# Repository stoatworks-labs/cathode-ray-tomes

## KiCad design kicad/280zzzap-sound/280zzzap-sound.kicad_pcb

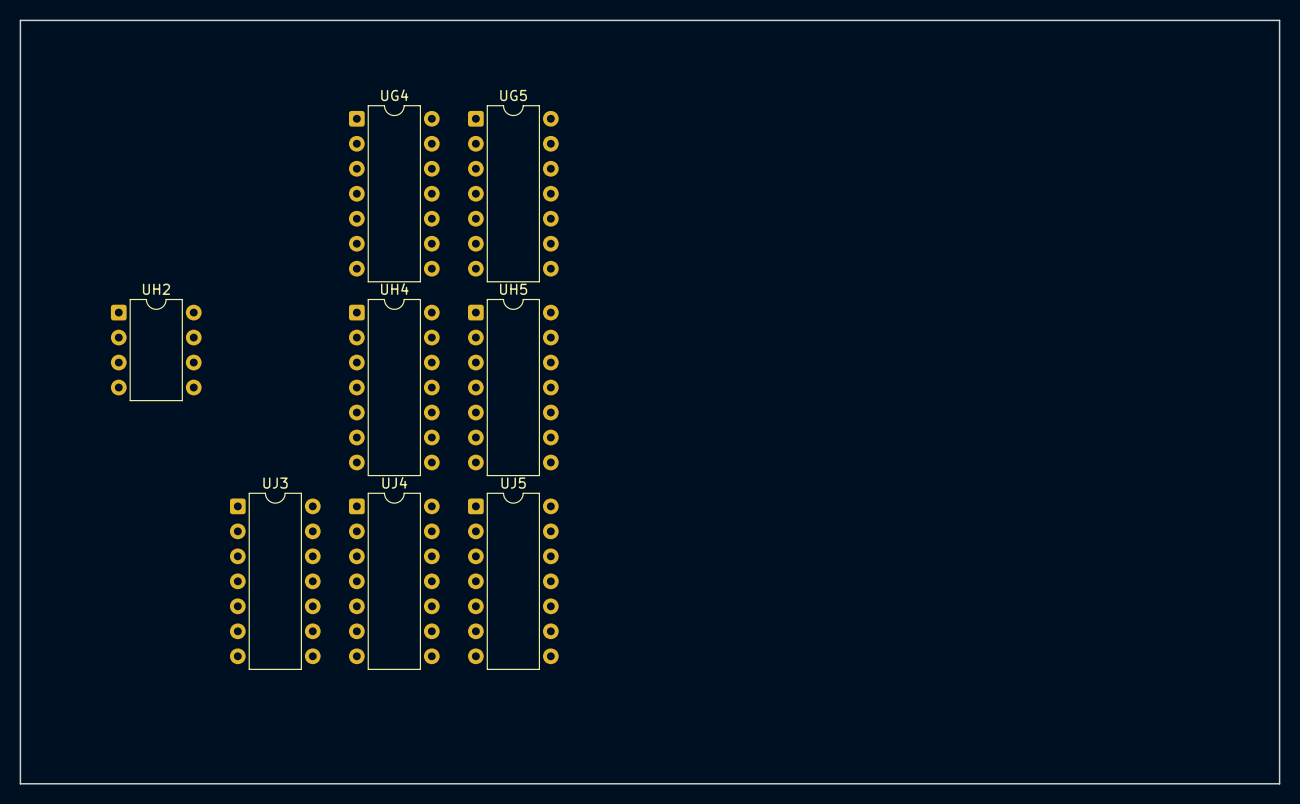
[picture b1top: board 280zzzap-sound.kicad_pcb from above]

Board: 2 copper layers, 128.0 x 77.6 mm, 8 parts (0 on the bottom side), 12 nets, no tracks yet.

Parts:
UG4, UG5: CD4016; DIP-14_W7.62mm
UH2: MC3340; DIP-8_W7.62mm
UH4, UH5: LM3900; DIP-14_W7.62mm
UJ3, UJ5: LM3900; DIP-14_W7.62mm
UJ4: CD4016; DIP-14_W7.62mm

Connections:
+5V: UG4.14, UG5.14, UH4.14, UH5.14, UJ3.14, UJ4.14, UJ5.14
GND: UG4.7, UG5.1, UG5.7, UH2.3, UH4.7, UH5.7, UJ3.7, UJ4.7, UJ5.7
unnamed: UG4.8, UH5.4
unnamed: UG5.3, UG5.8
unnamed: UG4.4, UH4.10
unnamed: UJ3.5, UJ4.13
unnamed: UJ3.10, UJ4.5
unnamed: UJ4.12, UJ5.5
unnamed: UG5.4, UH5.11
unnamed: UJ3.2, UJ4.2
unnamed: UJ3.13, UJ4.3
unnamed: UJ4.11, UJ5.2

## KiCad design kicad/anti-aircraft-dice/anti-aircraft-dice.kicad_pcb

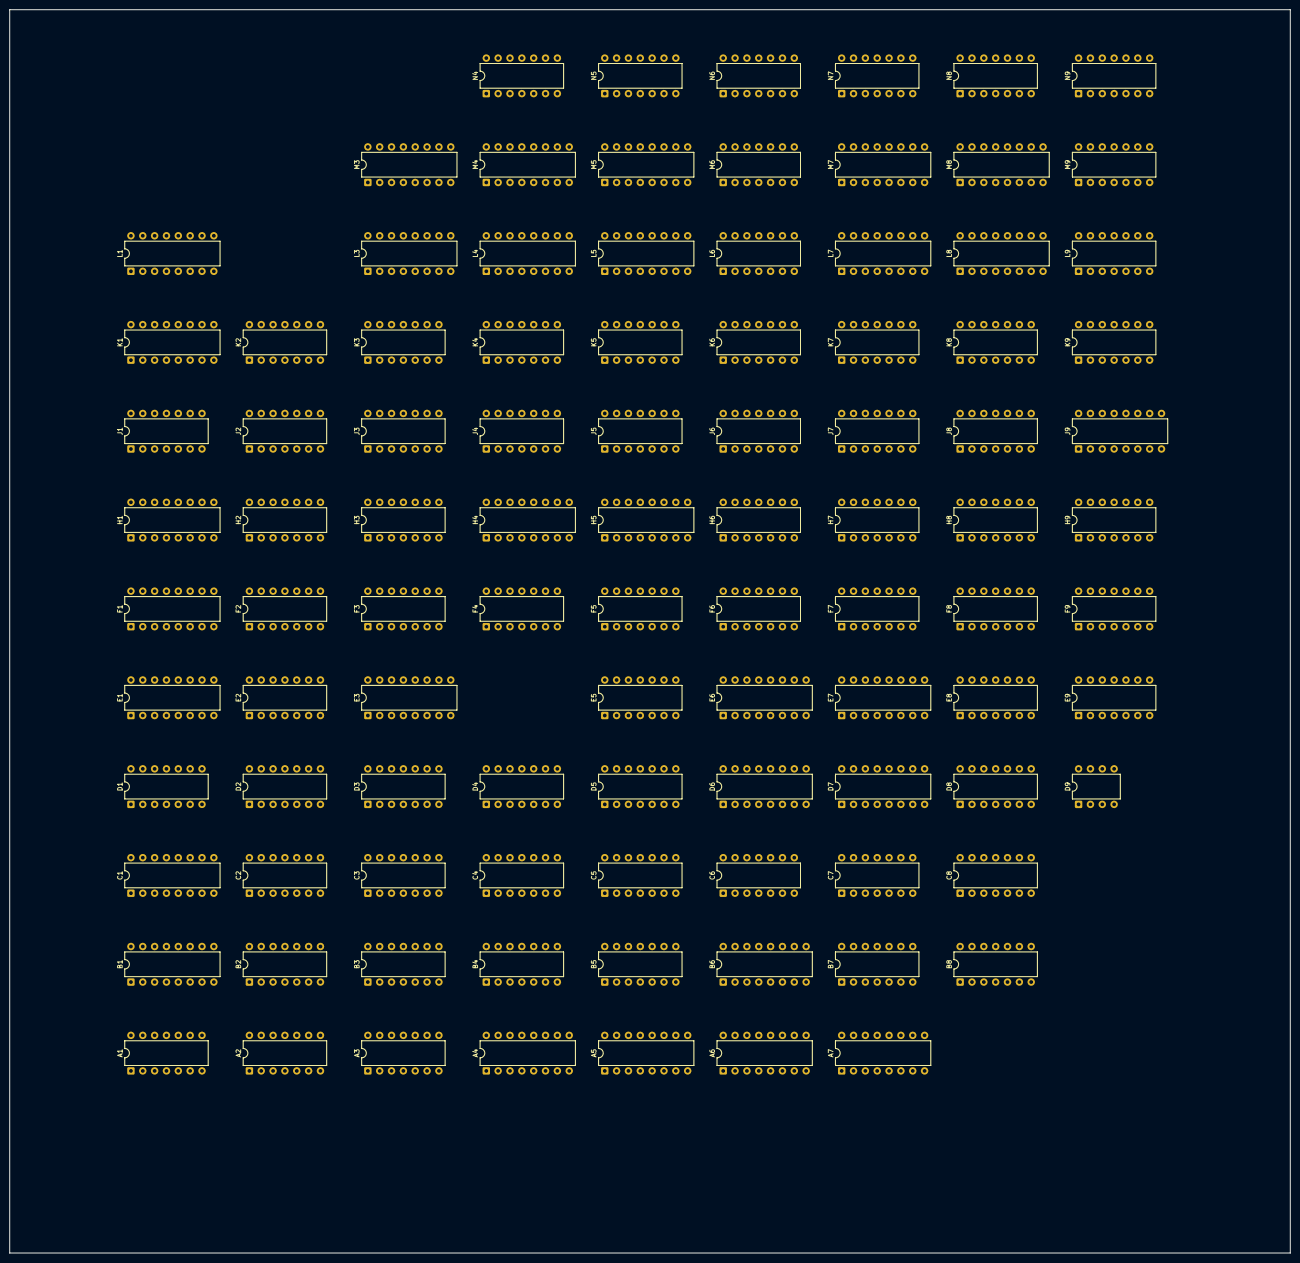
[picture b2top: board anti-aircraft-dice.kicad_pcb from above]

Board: 2 copper layers, 274.6 x 266.6 mm, 97 parts (0 on the bottom side), 319 nets, no tracks yet.

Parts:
A1: 7402; DIP-14_W7.62mm
A2: 7408; DIP-14_W7.62mm
A3: 7493; DIP-14_W7.62mm
A4, A5: 74153; DIP-16_W7.62mm
A6: 7448; DIP-16_W7.62mm
A7: 9312; DIP-16_W7.62mm
B1: 9602; DIP-16_W7.62mm
B2, B8: 7400; DIP-14_W7.62mm
B3: 7474; DIP-14_W7.62mm
B4, B5: 7490; DIP-14_W7.62mm
B6: 9312; DIP-16_W7.62mm
B7: 7402; DIP-14_W7.62mm
C1: 9602; DIP-16_W7.62mm
C2: 7400; DIP-14_W7.62mm
C3: 7402; DIP-14_W7.62mm
C4, C5: 7490; DIP-14_W7.62mm
C6: 7486; DIP-14_W7.62mm
C7: 7410; DIP-14_W7.62mm
C8: 7404; DIP-14_W7.62mm
D1, D8: 7474; DIP-14_W7.62mm
D2: 7427; DIP-14_W7.62mm
D3, D4: 7420; DIP-14_W7.62mm
D5: 7402; DIP-14_W7.62mm
D6, D7: 9316; DIP-16_W7.62mm
D9: 555; DIP-8_W7.62mm
E1: 9602; DIP-16_W7.62mm
E2: 7404; DIP-14_W7.62mm
E3, E6, E7: 9316; DIP-16_W7.62mm
E5: 7486; DIP-14_W7.62mm
E8: 7408; DIP-14_W7.62mm
E9: 7474; DIP-14_W7.62mm
F1: 9316; DIP-16_W7.62mm
F2, F7: 74107; DIP-14_W7.62mm
F3: 7402; DIP-14_W7.62mm
F4: 7408; DIP-14_W7.62mm
F5, F8: 7474; DIP-14_W7.62mm
F6: 7400; DIP-14_W7.62mm
F9: 7404; DIP-14_W7.62mm
H1, H4, H5: 9316; DIP-16_W7.62mm
H2: 7408; DIP-14_W7.62mm
H3, H9: 7400; DIP-14_W7.62mm
H6: 7420; DIP-14_W7.62mm
H7: 7402; DIP-14_W7.62mm
H8: 7432; DIP-14_W7.62mm
J1, J2: 7486; DIP-14_W7.62mm
J3: 7402; DIP-14_W7.62mm
J4, J5, J8: 7474; DIP-14_W7.62mm
J6: 74107; DIP-14_W7.62mm
J7: 7400; DIP-14_W7.62mm
J9: 74153; DIP-16_W7.62mm
K1: 82S123; DIP-16_W7.62mm
K2, K8, K9: 7474; DIP-14_W7.62mm
K3: 7404; DIP-14_W7.62mm
K4, K5: 7493; DIP-14_W7.62mm
K6: 7410; DIP-14_W7.62mm
K7: 7486; DIP-14_W7.62mm
L1: 9312; DIP-16_W7.62mm
L3, L4, L5: 74153; DIP-16_W7.62mm
L6: 7402; DIP-14_W7.62mm
L7, L8: 9316; DIP-16_W7.62mm
L9: 7400; DIP-14_W7.62mm
M3, M4: 7485; DIP-16_W7.62mm
M5: 74153; DIP-16_W7.62mm
M6: 7400; DIP-14_W7.62mm
M7, M8: 9316; DIP-16_W7.62mm
M9: 7408; DIP-14_W7.62mm
N4: 7404; DIP-14_W7.62mm
N5: 7450; DIP-14_W7.62mm
N6, N9: 7402; DIP-14_W7.62mm
N7: 7408; DIP-14_W7.62mm
N8: 7400; DIP-14_W7.62mm

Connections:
+5V: A1.14, A2.14, A3.5, A4.16, A5.16, A6.16, A7.16, B2.14, B3.14, B4.5, B5.5, B6.16, B7.14, B8.14, C2.14, C3.14, C4.5, C5.5, C6.14, C7.14, C8.14, D1.14, D2.14, D3.14, D4.14, D5.14, D6.16, D7.16, D8.14, D9.8, E2.14, E3.16, E5.14, E6.16, E7.16, E8.14, E9.14, F1.16, F2.14, F3.14, F4.14, F5.14, F6.14, F7.14, F8.14, F9.14, H1.16, H2.14, H3.14, H4.16, H5.16, H6.14, H7.14, H8.14, H9.14, J1.14, J2.14, J3.14, J4.14, J5.14, J6.14, J7.14, J8.14, J9.16, K1.16, K2.14, K3.14, K4.5, K5.5, K6.14, K7.14, K8.14, K9.14, L1.16, L3.16, L4.16, L5.16, L6.14, L7.16, L8.16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
A1-1: A1.1, C8.1
A1-3: A1.3, A1.4, A3.2, A3.3
A1-9: A1.9, A1.13, A2.10, A2.12
A1-10: A1.10, A1.11
A2-2: A2.2, A2.8
A2-3: A2.3, B1.4
A2-4: A2.4, A2.11
A2-6: A2.6, B1.12
A3-1: A3.1, A3.12
A4-3: A4.3, B4.1, B4.12
A4-4: A4.4, B5.1, B5.12
A4-5: A4.5, C4.1, C4.12
A4-6: A4.6, C5.1, C5.12
A4-7: A4.7, A6.7
A4-9: A4.9, A6.1
A4-10: A4.10, C5.9
A4-11: A4.11, C4.9
A4-12: A4.12, B5.9
A4-13: A4.13, B4.9
A5-3: A5.3, B4.8
A5-4: A5.4, B5.8
A5-5: A5.5, C4.8
A5-6: A5.6, C5.8
A5-7: A5.7, A6.2
A5-9: A5.9, A6.6
A5-10: A5.10, C5.11
A5-11: A5.11, C4.11, C5.14
A5-12: A5.12, B5.11
A5-13: A5.13, B4.11, B5.14
A6-4: A6.4, B7.4
A6-9: A6.9, B6.5
A6-10: A6.10, A7.9
A6-11: A6.11, B6.9
A6-12: A6.12, B6.4
A6-13: A6.13, A7.1
A6-14: A6.14, A7.4
A6-15: A6.15, B6.1
A7-15: A7.15, B7.9
ATTRACT: A1.2, C3.9, C3.12, D8.9, E8.2, E9.3, E9.11, H7.2
ATTRACT_n: B3.12, D8.8, H9.2, H9.12, K8.4, K8.13, K9.4, K9.13
B1-3: B1.3, C1.7
B1-5: B1.5, B2.4, B2.11, C3.11
B1-11: B1.11, B2.5, B2.8, C3.8
B1-13: B1.13, C1.9
B2-3: B2.3, B3.11
B3-2: B3.2, B8.11
B3-3: B3.3, C8.10
B4-14: B4.14, C3.13
B6-15: B6.15, B7.8
B7-1: B7.1, B8.2
B7-3: B7.3, C7.12
B7-6: B7.6, C7.8
B7-10: B7.10, B8.12
B7-13: B7.13, D6.3
B8-3: B8.3, B8.13
B8-4: B8.4, D7.15, J7.9, K6.3
B8-5: B8.5, D6.15, D7.7
B8-6: B8.6, C3.2, D6.9, D7.9
C2-2: C2.2, E2.9, F4.6, H3.12
C2-3: C2.3, E6.4
C2-4: C2.4, D1.2, D1.6, D2.5
C2-5: C2.5, D1.8, D2.9
C2-8: C2.8, D1.1
C2-10: C2.10, D2.10, E2.12
C2-11: C2.11, D1.13
C2-13: C2.13, D2.4, E2.13, E3.14
C3-1: C3.1, F6.5
C3-3: C3.3, C3.5, E6.9, E7.9, F6.3
C3-6: C3.6, K6.6
C3-10: C3.10, C4.14
C6-6: C6.6, D5.12
C6-11: C6.11, C7.9
C7-2: C7.2, C7.4, E8.8
C7-3: C7.3, C8.6
C7-11: C7.11, C8.8
C8-4: C8.4, N5.9
CLOCK: E6.2, E7.2, H4.2, H5.2, J4.9, M7.2, M8.2
CLOCK_n: F1.2, H1.2, J4.3, J4.8, J4.12, N7.10, N7.12
COMP_HIT_n: C2.6, E1.5
COMP_SYNC: B3.1, E1.13, J2.3
D2-3: D2.3, D2.11, D3.6
D2-6: D2.6, F3.8
D2-8: D2.8, F3.9
D3-1: D3.1, H2.11
D3-2: D3.2, E3.13
D3-4: D3.4, E3.12
D3-5: D3.5, E3.11
D3-10: D3.10, D3.12, D3.13
D4-1: D4.1, D5.13
D4-2: D4.2, E5.6
D4-6: D4.6, F4.9
D5-1: D5.1, D6.5
D5-3: D5.3, D5.4, D6.4
D5-8: D5.8, E5.3, E5.9
D5-9: D5.9, E5.10, E5.11
D5-10: D5.10, D5.11
D6-1: D6.1, D7.1, F6.11
D8-2: D8.2, E8.3
D8-10: D8.10, D9.4, E8.11
D8-11: D8.11, F9.12
D9-3: D9.3, F9.13
DELAY_L: C1.10, H8.12
DELAY_R: C1.6, H8.2
DIR_SELECT_n: F2.3, H3.2, J1.2, J1.4, J1.10, J1.12
E1-7: E1.7, K2.13
E1-11: E1.11, N9.4
E2-2: E2.2, E3.3
E2-3: E2.3, F3.10
E2-8: E2.8, E6.5
E2-10: E2.10, E3.9
E2-11: E2.11, E3.15
E3-10: E3.10, H2.13, J2.11
E5-5: E5.5, E5.8
E6-1: E6.1, E7.1, F5.5, F7.13
E6-3: E6.3, H3.11
E6-15: E6.15, E7.7, F6.2
E7-15: E7.15, F7.12, M9.1
E8-12: E8.12, F8.2, F9.4
E9-1: E9.1, E9.13, F8.9
E9-5: E9.5, E9.12
F1-7: F1.7, H1.15, H3.4
F1-9: F1.9, H1.9, H3.6
F1-15: F1.15, F2.9, H2.2
F2-2: F2.2, F3.3
F2-5: F2.5, H2.1
F3-1: F3.1, H1.6
F3-11: F3.11, J7.8
F3-12: F3.12, F6.8
F4-3: F4.3, F5.3
F4-10: F4.10, F6.6
F6-1: F6.1, F6.10, M9.3
F7-3: F7.3, M9.2
F7-5: F7.5, M9.10
F7-9: F7.9, M7.15, M9.9
F7-10: F7.10, M7.1, M8.1, N8.3
F8-4: F8.4, F9.3
F8-5: F8.5, F8.12
F9-1: F9.1, N5.4, N5.10, N6.13
F9-2: F9.2, N6.5
FIRE_LEFT: F5.1, H7.5, J8.8, J9.15
FIRE_LEFT_n: F6.13, J8.9
FIRE_RIGHT: H7.6, J8.6, J9.1
FIRE_RIGHT_n: J8.5, M6.4, N8.1
FLASH: A3.8, E5.4, K7.9
GND: A1.7, A2.7, A3.10, A4.1, A4.8, A4.15, A5.1, A5.8, A5.15, A6.8, A7.2, A7.3, A7.5, A7.6, A7.7, A7.8, B2.7, B3.7, B4.6, B4.7, B4.10, B5.6, B5.7, B5.10, B6.2, B6.3, B6.6, B6.7, B6.8, B7.7, B8.7, C1.4, C1.12, C2.7, C3.7, C4.6, C4.7, C4.10, C5.6, C5.7, C5.10, C6.7, C7.7, C8.7, D1.7, D2.7, D3.7, D4.7, D5.7, D6.8, D7.3, D7.4, D7.5, D7.6, D7.8, D8.7, D9.1, E1.12, E2.7, E3.4, E3.5, E3.8, E5.7, E6.6, E6.8, E7.5, E7.6, E7.8, E8.7, E9.7, F1.5, F1.6, F1.8, F2.7, F3.7, F4.7, F5.7, F6.7, F7.7, F8.7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
H1: C8.11, H4.14, J9.14, K8.2, K9.2, L5.6, M5.6
H1-5: H1.5, H3.3
H2: B6.11, H4.13, J9.2, K8.12, K9.12, L5.5, L5.10, M5.5, M5.10
H2-3: H2.3, H2.10, H3.5
H3-8: H3.8, L1.10
H4: B6.12, H4.12, J5.11, L3.6, L4.6, L5.4, L5.11, M5.4, M5.11
H4-15: H4.15, H5.7
H5-15: H5.15, J6.12
H6-1: H6.1, H7.13
H6-2: H6.2, K7.8
H6-6: H6.6, M9.13
H6-8: H6.8, J4.2
H7-3: H7.3, H7.4
H7-8: H7.8, K7.6, K7.12
H7-9: H7.9, K7.3, K7.13
H7-10: H7.10, H7.11
H7-12: H7.12, J2.6
H8: A7.10, B6.10, F4.2, H4.11, H6.9, L3.5, L3.10, L4.5, L4.10, L5.12, M5.12
H8-1: H8.1, H9.6
H8-3: H8.3, J8.1
H8-11: H8.11, J8.13
H8-13: H8.13, H9.8
H9-1: H9.1, L9.11
H9-3: H9.3, J9.5
H9-4: H9.4, J9.7, K9.3, K9.11
H9-9: H9.9, J9.9, K8.3, K8.11
H9-11: H9.11, J9.11
H9-13: H9.13, N9.1
H16: A4.14, A5.14, A6.5, F4.1, H5.14, J2.10, K3.5
H16_n: K3.6, L3.4, L3.11, L4.4, L4.11
H32: A4.2, A5.2, C6.1, H5.13, J2.9
H64: C6.13, H5.12, H6.10, J3.6, K3.3
H64_n: K3.4, L3.12, L4.12
H128: C6.9, H5.11, H6.12, J5.12
H128_xor_H256: C6.8, C7.10, C8.13
H128_xor_H256_n: B8.1, C8.12, M6.1
H256: C6.2, C6.10, C6.12, H6.13, J5.10, J6.3, N7.9
H256_n: J6.2, N7.13
H256_xor_H32: B7.2, C6.3, C8.9, N6.6
HIT_DETECT: B2.1, B2.2, B2.6, C2.9, C2.12
HRESET: J3.2, J4.6, J5.3, K4.14
HRESET_n: H4.1, H5.1, J4.5, J6.13
HSYNC: D6.2, D7.2, J2.1, J3.3, J3.4, K2.11, L7.2, L8.2
HSYNC_n: J3.1, J3.5, J7.5
J1-3: J1.3, K1.12
J1-6: J1.6, K1.11
J1-8: J1.8, K1.13
J1-11: J1.11, K1.10
J2-8: J2.8, M6.2
J4-11: J4.11, N4.4
J5-2: J5.2, K6.8
J5-8: J5.8, N8.2
J7-2: J7.2, J7.6, J7.12
J7-3: J7.3, J8.4
J7-11: J7.11, J8.10
K1-1: K1.1, L1.1
K1-2: K1.2, L1.2
K1-3: K1.3, L1.3
K1-4: K1.4, L1.4
K1-5: K1.5, L1.5
K1-6: K1.6, L1.6
K1-7: K1.7, L1.7
K1-9: K1.9, L1.9
K6-12: K6.12, N9.8
K6-13: K6.13, L8.15, L9.9, M6.12
K7-10: K7.10, K7.11
L3-7: L3.7, M3.13
L3-9: L3.9, M3.15
L4-7: L4.7, M4.13
L4-9: L4.9, M4.15
L5-7: L5.7, M3.10
L5-9: L5.9, M3.12
L6-1: L6.1, L7.5
L6-2: L6.2, L6.13, L7.4
L6-5: L6.5, M6.11
L6-6: L6.6, M6.8
L6-10: L6.10, L7.3
L7-1: L7.1, L8.1, M6.6
L7-9: L7.9, L8.9, L9.8, N9.12
L7-15: L7.15, L8.7, L9.10
L9-2: L9.2, N9.13
L9-3: L9.3, M9.12
L9-4: L9.4, M7.7, M8.15
L9-5: L9.5, M6.9, M9.8
L9-6: L9.6, M7.9, M8.9, N9.9, N9.11
L9-12: L9.12, L9.13
LA: H3.13, K8.5, L3.14, L5.14, N6.2
LARGE_LEFT_MISSILE: B2.10, C3.4, J7.13
LARGE_RIGHT_MISSILE: B2.13, J7.1, N9.10
LA_or_LB: B7.12, C2.1, N4.10, N5.5
LB: K8.9, L3.2, L5.2, N6.3
LB_n: D5.6, K8.8
LEFT_MISSILE_WIN: A2.5, D4.5, F3.13
LEFT_MISSILE_n: B8.9, F4.8
LMH1: C6.5, E6.14
LMH2: E5.12, E6.13
LMH3: E5.13, E6.12
LMH4: E6.11, F6.9
LMV1: C6.4, D6.14
LMV2: D6.13, E5.1
LMV3: D6.12, E5.2, K6.5
LMV4: D6.11, J7.10, K6.4
LT_HIT: A1.5, B1.10, B7.11, C1.11, D4.4, D5.2, D5.5
LT_HIT_n: A2.13, B1.9, F4.5, F6.4, J8.11
M3-3: M3.3, N4.8
M3-6: M3.6, N7.1
M4-3: M4.3, N4.12
M4-6: M4.6, N7.4
M4-10: M4.10, M5.7
M4-12: M4.12, M5.9
M6-3: M6.3, N6.12
M8-4: M8.4, N8.11
M8-5: M8.5, N8.8
M8-6: M8.6, M9.6, N8.10, N8.12
MISSILE_VRESET: F5.8, F6.12, M6.5
N4-9: N4.9, N5.6
N4-11: N4.11, N5.3, N6.1
N4-13: N4.13, N5.8
N5-1: N5.1, N5.2, N6.4
N7-2: N7.2, N7.11
N7-3: N7.3, N9.6
N7-5: N7.5, N7.8
N7-6: N7.6, N9.5
N9-2: N9.2, N9.3
PH1: H1.14, J1.13
PH2: H1.13, J1.5
PH3: H1.12, J1.1
PH4: H1.11, J1.9
PLANE_EN: B2.9, B2.12, H2.8, H3.9
PLANE_RESET: D3.9, K2.8
PLANE_RESET_n: F1.1, F2.10, H1.1, H3.10, K2.9
Q: D8.1, E8.13, E9.10, F9.10
RA: K9.5, L4.14, M5.14, N6.8, N8.13
RANDOM_CLOCK: D1.3, D1.11, D3.8, E2.1, F2.12
RA_n: K9.6, L6.8
RA_nor_RB: C8.3, L6.11, N5.13, N6.10, N8.9
RB: K9.9, L4.2, M5.2, N6.9
RIGHT_MISSILE_WIN: A2.1, H6.4, L6.4
RIGHT_MISSILE_n: B8.10, M9.11
RMH1: J2.4, M8.14
RMH2: K7.1, M8.13
RMH3: K7.2, M8.12
RMH4: M6.10, M8.11
RMV1: J2.5, L7.14
RMV2: K7.4, L7.13
RMV3: K6.1, K7.5, L7.12
RMV4: K6.2, L7.11, M6.13
RT_HIT: A1.6, B1.6, C1.5, H6.5, L6.3, L6.9, L6.12
RT_HIT_n: A2.9, B1.7, J8.3, L9.1, M9.5
SCOREV_n: B7.5, C7.6, F5.12, L3.1, L3.15, L4.1, L4.15, L5.1, L5.15, M5.1, M5.15, N6.11
START: B4.2, B4.3, B5.2, B5.3, C4.2, C4.3, C5.2, C5.3, D8.5, E1.4
START_n: D8.6, D8.13, D9.2, E3.1
V1: K3.1, K4.1, K4.12, K6.9, L1.11, M4.9
V1_n: K3.2, M3.9
V2: A7.11, K3.9, K4.9, K6.10, L1.12, M4.11
V2_n: K3.8, M3.11
V4: A7.12, F5.11, K3.11, K4.8, L1.13, M4.14
V4_n: K3.10, M3.14
V8: A7.13, B6.13, J3.9, K3.13, K4.11, K5.14, M4.1
V8_n: E3.2, F5.10, H2.12, K3.12, M3.1
V16: C7.1, C8.5, K5.1, K5.12
V32: E8.9, K5.9
V64: E8.10, J2.12, K5.8
V128: C7.5, C7.13, F8.3, F8.11, J2.13, J6.9, K5.11
V256: D8.3, H9.5, H9.10, J6.5, K6.11
V256_n: F4.12, J6.6
VCC: A6.3, B3.4, B3.10, C1.3, C1.13, D1.4, D1.10, D1.12, D6.6, D6.7, D7.10, D8.4, D8.12, E1.3, E3.6, E3.7, E6.7, E6.10, E7.3, E7.4, E7.10, E9.2, F1.3, F1.4, F1.10, F2.1, F2.4, F2.8, F2.11, F2.13, F5.2, F5.4, F5.13, F7.1, F7.4, F7.8, F7.11, F8.1, F8.10, F8.13, H1.3, H1.7, H1.10, H4.3, H4.4, H4.5, H4.6, H4.7, H4.9, H4.10, H5.3, H5.4, H5.5, H5.6, H5.9, H5.10, J4.1, J4.4, J4.10, J4.13, J5.1, J5.4, J5.13, J6.1, J6.4, J6.8, J6.11, J8.2, J8.12, K2.10, K2.12, K8.1, K8.10, K9.1, K9.10, L3.3, L3.13, L4.3, L4.13, L5.3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
VCOUNT_n: D6.10, F4.11, L7.10
VPLANE_ENABLE: A1.12, E2.4, H2.9
VRESET: A1.8, F4.4, H3.1, J3.12, J5.6, K4.2, K4.3, K5.2, K5.3, M9.4
VRESET_n: A3.14, B3.13, F3.2, H1.4, J5.5, J6.10, J7.4
VSYNC: J3.10, J3.11
VSYNC_n: F4.13, J2.2, J3.8, J3.13

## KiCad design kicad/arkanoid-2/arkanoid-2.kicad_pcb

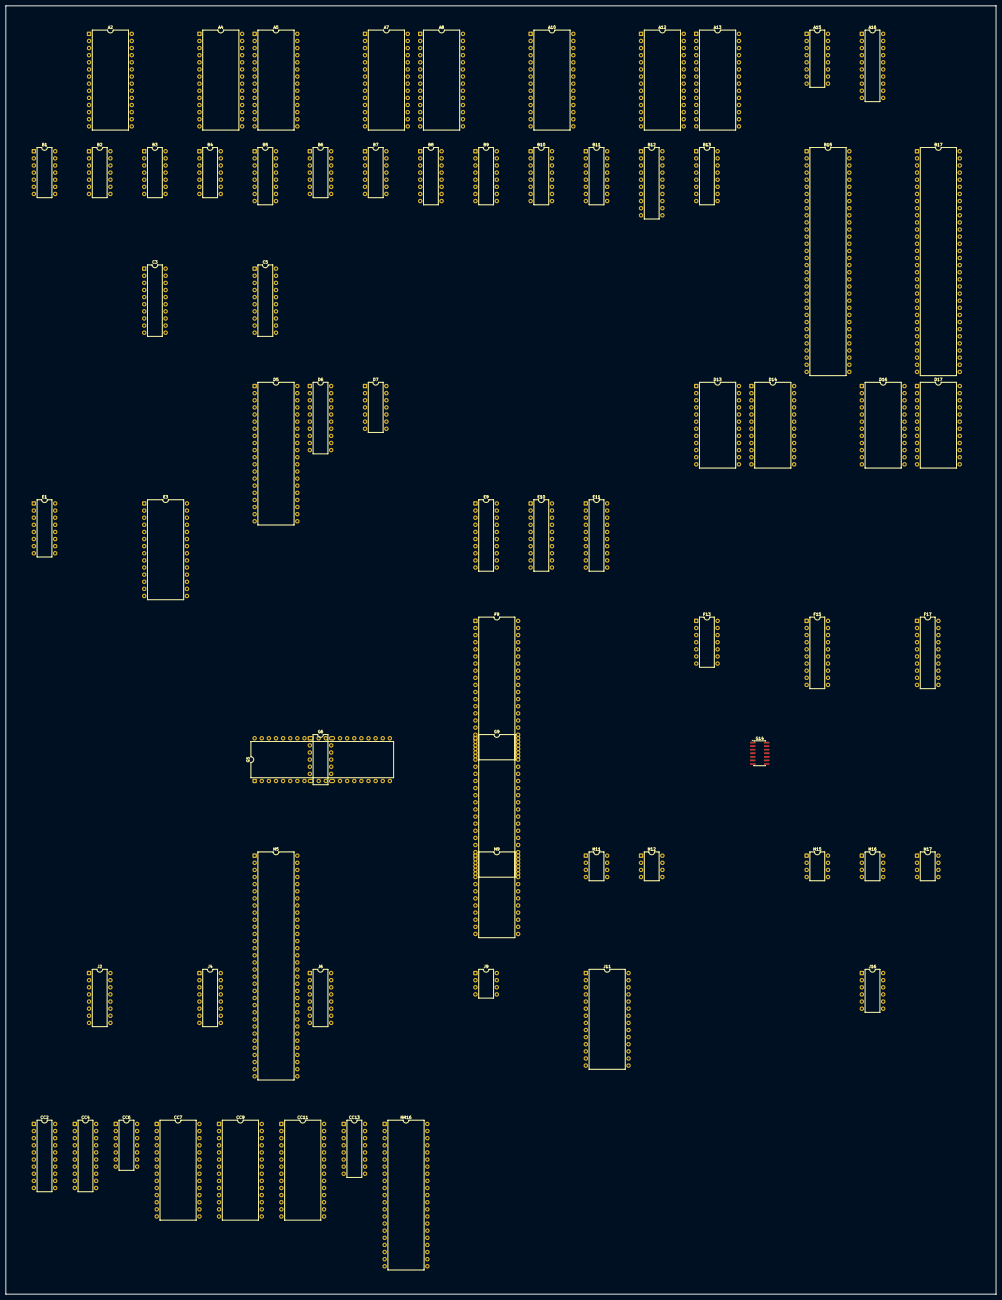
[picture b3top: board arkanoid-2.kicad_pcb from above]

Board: 2 copper layers, 353.4 x 459.8 mm, 68 parts (0 on the bottom side), 338 nets, no tracks yet.

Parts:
A2, A4, A5, A7, A8, A10, A12, A13: 27C512; DIP-28_W15.24mm
A15: 74LS174; DIP-16_W7.62mm
A16: 74LS273; DIP-20_W7.62mm
B1: 74F04; DIP-14_W7.62mm
B2, B6: 74LS08; DIP-14_W7.62mm
B3, B4, B7: 74LS74; DIP-14_W7.62mm
B5: 74LS174; DIP-16_W7.62mm
B8, B9, B10, B11: 74LS157; DIP-16_W7.62mm
B12: 74LS245_Notristate; DIP-20_W7.62mm
B13: 74LS367; DIP-16_W7.62mm
B15: YM3909; DIP-64_W15.24mm
B17: YM3906; DIP-64_W15.24mm
C3: PAL16L8’; DIP-20_W7.62mm
C5: 74LS245; DIP-20_W7.62mm
CC2: PAL16L8’; DIP-20_W7.62mm
CC4: 74LS245; DIP-20_W7.62mm
CC6: 74F32; DIP-14_W7.62mm
CC7: MB8464; DIP-28_W15.24mm
CC9, CC11: 27512; DIP-28_W15.24mm
CC13: 74LS367; DIP-16_W7.62mm
D5: Z80CPU; DIP-40_W15.24mm
D6: PAL16L8’; DIP-20_W7.62mm
D7: 74LS02; DIP-14_W7.62mm
D13, D14, D16, D17: HM6116P-3; DIP-24_W15.24mm
E1: 74LS174; DIP-16_W7.62mm
E3: 27512; DIP-28_W15.24mm
E9: PAL16L8’; DIP-20_W7.62mm
E10, E11: 74LS245; DIP-20_W7.62mm
F9: Z80CPU; DIP-40_W15.24mm
F13: HD14584BP; DIP-14_W7.62mm
F15, F17: MB7124; DIP-20_W7.62mm
G5: INTEL8042 / M-CHIP; DIP-40_W15.24mm
G6: HD14584BP; DIP-14_W7.62mm
G9: YM2203; DIP-40_W15.24mm
G14: 74HC4024; SOIC-14_3.9x8.7mm_P1.27mm
H5: X1-004; DIP-64_W15.24mm
H9: uPD4701A; DIP-24_W15.24mm
H11: YM3014; DIP-8_W7.62mm
H12: RC4558; DIP-8_W7.62mm
H15, H16, H17: R0-012; DIP-8_W7.62mm
HH16: X1-003; DIP-42_W15.24mm
J2, J4, J6: X2-003; DIP-16_W7.62mm
J9: TL7705A; DIP-8_W7.62mm
J11: PC050CM; DIP-28_W15.24mm
J16: HA1388; DIP-12_W7.62mm

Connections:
/CPU/1P_RESET_CNT: E1.10, H9.3
/CPU/2P_RESET_CNT: E1.7, H9.6
/CPU/H2B: B2.4, B12.18, G9.38
/CPU/H2H4: B4.9, C3.6
/CPU/H4B: B2.5, B12.12, B13.1, B13.15, CC6.2, CC6.13, CC13.1, CC13.15, D6.11
/CPU/MA0: B11.13, B13.10, CC9.10, CC11.10, F9.30
/CPU/MA1: B11.10, B13.12, CC9.9, CC11.9, F9.31
/CPU/MA2: B9.3, B13.14, CC9.8, CC11.8, F9.32
/CPU/MA3: B10.10, B13.2, CC9.7, CC11.7, F9.33
/CPU/MA4: B11.3, B13.4, CC9.6, CC11.6, F9.34
/CPU/MA5: B11.6, B13.6, CC9.5, CC11.5, F9.35
/CPU/MA6: B10.13, CC9.4, CC11.4, CC13.4, F9.36
/CPU/MA7: B10.6, CC9.3, CC11.3, CC13.6, F9.37
/CPU/MA8: B8.3, CC9.25, CC11.25, CC13.10, F9.38
/CPU/MA9: B8.6, CC9.24, CC11.24, CC13.12, E9.7, F9.39
/CPU/MA10: B9.13, CC9.21, CC11.21, CC13.14, E9.6, F9.40
/CPU/MA11: B10.3, B17.27, CC9.23, CC11.23, CC13.2, E9.5, F9.1
/CPU/MA12: B9.10, CC9.2, CC11.2, E9.4, F9.2
/CPU/MA13: CC9.26, CC11.26, E9.3, F9.3
/CPU/MA14: D6.2, E9.2, F9.4
/CPU/MA15: D6.1, E9.1, F9.5
/CPU/MBSWD0: B5.2, B6.2, D6.6
/CPU/MD0: B5.3, C5.9, CC9.11, CC11.11, E10.3, E11.3, F9.14
/CPU/MD1: B5.4, C5.8, CC9.12, CC11.12, E10.2, E11.2, F9.15
/CPU/MD2: B5.6, C5.7, CC9.13, CC11.13, E10.9, E11.9, F9.12
/CPU/MD3: B5.14, C5.6, CC9.15, CC11.15, E10.8, E11.8, F9.8
/CPU/MD4: B5.13, C5.5, CC9.16, CC11.16, E10.7, E11.7, F9.7
/CPU/MD5: B5.11, C5.4, CC9.17, CC11.17, E10.6, E11.6, F9.9
/CPU/MD6: C5.3, CC9.18, CC11.18, E10.5, E11.5, F9.10
/CPU/MD7: C5.2, CC9.19, CC11.19, E10.4, E11.4, F9.13
/CPU/MR2A14: B5.7, CC9.27, D6.5
/CPU/MR2A15: B2.9, B5.5
/CPU/MRA14: CC11.27, D6.14
/CPU/MRA15: B2.8, CC11.1
/CPU/SA0: B11.14, D5.30, E3.10, G5.9, G9.37, H9.13
/CPU/SA1: B11.11, D5.31, E3.9, H9.14
/CPU/SA2: B9.2, D5.32, E3.8
/CPU/SA3: B10.11, D5.33, E3.7
/CPU/SA4: B11.2, D5.34, E3.6
/CPU/SA5: B11.5, D5.35, E3.5
/CPU/SA6: B10.14, D5.36, E3.4
/CPU/SA7: B10.5, D5.37, E3.3
/CPU/SA8: B8.2, D5.38, E3.25
/CPU/SA9: B8.5, D5.39, E3.24
/CPU/SA10: B9.14, D5.40, E3.21
/CPU/SA11: B10.2, CC2.5, D5.1, E3.23
/CPU/SA12: B9.11, CC2.4, D5.2, E3.2
/CPU/SA13: CC2.3, D5.3
/CPU/SA14: CC2.2, D5.4
/CPU/SA15: CC2.1, D5.5, E3.1
/CPU/SBANK0: CC2.11, E1.15
/CPU/SBANK1: CC2.9, E1.12
/CPU/SD0: CC4.9, D5.14, E1.14, E3.11, G5.12, G9.40, H9.16
/CPU/SD1: CC4.8, D5.15, E1.13, E3.12, G5.13, G9.2, H9.17
/CPU/SD2: CC4.7, D5.12, E1.11, E3.13, G5.14, G9.3, H9.18
/CPU/SD3: CC4.6, D5.8, E1.6, E3.15, G5.15, G9.4, H9.19
/CPU/SD4: CC4.5, D5.7, E1.4, E3.16, G5.16, G9.5, H9.20
/CPU/SD5: CC4.4, D5.9, E1.3, E3.17, G5.17, G9.6, H9.21
/CPU/SD6: CC4.3, D5.10, E3.18, G5.18, G9.7, H9.22
/CPU/SD7: CC4.2, D5.13, E3.19, G5.19, G9.8, H9.23
/CPU/SHA0: B11.12, CC7.10
/CPU/SHA1: B11.9, CC7.9
/CPU/SHA2: B9.4, CC7.8
/CPU/SHA3: B10.9, CC7.7
/CPU/SHA4: B11.4, CC7.6
/CPU/SHA5: B11.7, CC7.5
/CPU/SHA6: B10.12, CC7.4
/CPU/SHA7: B10.7, CC7.3
/CPU/SHA8: B8.4, CC7.25
/CPU/SHA9: B8.7, CC7.24
/CPU/SHA10: B9.12, CC7.21
/CPU/SHA11: B10.4, CC7.23
/CPU/SHA12: B9.9, CC7.2
/CPU/SHD0: C5.11, CC4.11, CC7.11
/CPU/SHD1: C5.12, CC4.12, CC7.12
/CPU/SHD2: C5.13, CC4.13, CC7.13
/CPU/SHD3: C5.14, CC4.14, CC7.15
/CPU/SHD4: C5.15, CC4.15, CC7.16
/CPU/SHD5: C5.16, CC4.16, CC7.17
/CPU/SHD6: C5.17, CC4.17, CC7.18
/CPU/SHD7: C5.18, CC4.18, CC7.19
/CPU/SRA13: CC2.18, E3.26
/CPU/SRA14: CC2.19, E3.27
/CPU/VA11: B17.28, D6.7
/CPU/YMCS: B3.6, C3.11
/CPU/~BGTRNSP: B6.4, B15.2, E9.14
/CPU/~BNKSW: B1.5, B5.9, E9.15
/CPU/~DIALCS: CC2.17, H9.15
/CPU/~MCUCS: CC2.16, G5.6
/CPU/~MCURESET: B2.11, G5.4
/CPU/~MMREQ: D6.3, E9.8, F9.19
/CPU/~MRD: B1.9, B8.13, B17.2, C5.1, E10.1, E11.1, F9.21
/CPU/~MRESET: B2.1, B5.1, B17.29, F9.26, J9.5
/CPU/~MRFSH: D6.4, E9.9, F9.28
/CPU/~MROM2CS: CC9.22, D6.13
/CPU/~MROMCS: CC11.22, D6.12
/CPU/~MSHRAMEN: C3.16, C5.19
/CPU/~MSHRAMRQ: C3.1, E9.18
/CPU/~MWAIT: C3.14, F9.24
/CPU/~MWR: C3.2, E9.11, F9.22
/CPU/~OBJCODEHI: B6.5, D6.9, E9.17
/CPU/~OBJCODELO: D6.8, E9.16
/CPU/~OBJORVRAMEN: C3.5, E9.19
/CPU/~OBJRAM1CS: D6.18, D13.18
/CPU/~OBJRAM2CS: D6.17, D14.18
/CPU/~OBJRAM3CS: D6.16, D16.18
/CPU/~OBJRAM4CS: D6.15, D17.18
/CPU/~SBNKSW: CC2.14, E1.9
/CPU/~SHRAMCS: C3.17, CC7.20
/CPU/~SHRAMENB: B8.1, B9.1, B10.1, B11.1, C3.19
/CPU/~SHRAMRD: B8.12, CC7.22
/CPU/~SHRAMWR: C3.18, CC7.27
/CPU/~SMREQ: CC2.7, D5.19
/CPU/~SRD: B8.14, CC4.1, D5.21, G5.8, G9.36
/CPU/~SRESET: B2.3, B2.12, D5.26, E1.1, G9.24
/CPU/~SRFSH: CC2.8, D5.28
/CPU/~SROMCS: CC2.12, E3.22
/CPU/~SSHRAMEN: C3.15, CC4.19
/CPU/~SSHRAMRQ: C3.3, CC2.13
/CPU/~SWAIT: C3.13, D5.24
/CPU/~SWR: C3.4, CC2.6, D5.22, G5.10, G9.35
/CPU/~VRAMWR: B6.1, B17.3, E9.13
/CPU/~YMCS2: B3.4, B3.9, C3.9
/CPU/~YMCS: B3.2, CC2.15, G9.34
/CPU/~YMIRQ: F9.17, G9.25
/GFX/CH0: A2.10, A4.10, A5.10, A7.10, A8.10, A10.10, A12.10, A13.10, B17.35
/GFX/CH1: A2.9, A4.9, A5.9, A7.9, A8.9, A10.9, A12.9, A13.9, B17.36
/GFX/CH2: A2.8, A4.8, A5.8, A7.8, A8.8, A10.8, A12.8, A13.8, B17.37
/GFX/CH4: A2.6, A4.6, A5.6, A7.6, A8.6, A10.6, A12.6, A13.6, B17.38
/GFX/CK12M: B15.3, B17.62
/GFX/COL0: B15.28, F15.1, F17.1
/GFX/COL1: B15.27, F15.2, F17.2
/GFX/COL2: B15.26, F15.3, F17.3
/GFX/COL3: B15.25, F15.4, F17.4
/GFX/COL4: B15.24, F15.5, F17.5
/GFX/COL5: B15.23, F15.16, F17.16
/GFX/COL6: B15.22, F15.17, F17.17
/GFX/COL7: B15.21, F15.18, F17.18
/GFX/COL8: B15.20, F15.19, F17.19
/GFX/GA5: A2.5, A4.5, A5.5, A7.5, A8.5, A10.5, A12.5, A13.5, A16.15
/GFX/GA6: A2.4, A4.4, A5.4, A7.4, A8.4, A10.4, A12.4, A13.4, A16.16
/GFX/GA7: A2.3, A4.3, A5.3, A7.3, A8.3, A10.3, A12.3, A13.3, A16.2
/GFX/GA8: A2.25, A4.25, A5.25, A7.25, A8.25, A10.25, A12.25, A13.25, A16.5
/GFX/GA9: A2.24, A4.24, A5.24, A7.24, A8.24, A10.24, A12.24, A13.24, A16.6
/GFX/GA10: A2.21, A4.21, A5.21, A7.21, A8.21, A10.21, A12.21, A13.21, A16.9
/GFX/GA11: A2.23, A4.23, A5.23, A7.23, A8.23, A10.23, A12.23, A13.23, A16.12
/GFX/GA12: A2.2, A4.2, A5.2, A7.2, A8.2, A10.2, A12.2, A13.2, A16.19
/GFX/GA13: A2.26, A4.26, A5.26, A7.26, A8.26, A10.26, A12.26, A13.26, A15.5
/GFX/GA14: A2.27, A4.27, A5.27, A7.27, A8.27, A10.27, A12.27, A13.27, A15.2
/GFX/GA15: A2.1, A4.1, A5.1, A7.1, A8.1, A10.1, A12.1, A13.1
/GFX/GCE: A2.20, A5.20, A8.20, A12.20, B1.10
/GFX/GDA0: A12.11, A13.11, B15.56
/GFX/GDA1: A12.12, A13.12, B15.57
/GFX/GDA2: A12.13, A13.13, B15.58
/GFX/GDA3: A12.15, A13.15, B15.59
/GFX/GDA4: A12.16, A13.16, B15.60
/GFX/GDA5: A12.17, A13.17, B15.61
/GFX/GDA6: A12.18, A13.18, B15.62
/GFX/GDA7: A12.19, A13.19, B15.63
/GFX/GDB0: A8.11, A10.11, B15.48
/GFX/GDB1: A8.12, A10.12, B15.49
/GFX/GDB2: A8.13, A10.13, B15.50
/GFX/GDB3: A8.15, A10.15, B15.51
/GFX/GDB4: A8.16, A10.16, B15.52
/GFX/GDB5: A8.17, A10.17, B15.53
/GFX/GDB6: A8.18, A10.18, B15.54
/GFX/GDB7: A8.19, A10.19, B15.55
/GFX/GDC0: A5.11, A7.11, B15.40
/GFX/GDC1: A5.12, A7.12, B15.41
/GFX/GDC2: A5.13, A7.13, B15.42
/GFX/GDC3: A5.15, A7.15, B15.43
/GFX/GDC4: A5.16, A7.16, B15.44
/GFX/GDC5: A5.17, A7.17, B15.45
/GFX/GDC6: A5.18, A7.18, B15.46
/GFX/GDC7: A5.19, A7.19, B15.47
/GFX/GDD0: A2.11, A4.11, B15.30
/GFX/GDD1: A2.12, A4.12, B15.31
/GFX/GDD2: A2.13, A4.13, B15.34
/GFX/GDD3: A2.15, A4.15, B15.35
/GFX/GDD4: A2.16, A4.16, B15.36
/GFX/GDD5: A2.17, A4.17, B15.37
/GFX/GDD6: A2.18, A4.18, B15.38
/GFX/GDD7: A2.19, A4.19, B15.39
/GFX/H: B12.4, B12.5, B12.6, B17.40
/GFX/H2: B12.2, B17.41
/GFX/H4: B1.1, B12.8, B17.42
/GFX/H8: B12.9, B17.43
/GFX/H8B: A15.9, A16.11, B12.11
/GFX/H8R: A2.7, A4.7, A5.7, A7.7, A8.7, A10.7, A12.7, A13.7, B17.34
/GFX/HX: B12.7, B17.39
/GFX/OBJRD: B17.30, CC6.5
/GFX/PXCK6M: B12.13, F13.11, G5.2
/GFX/SPBANK1: B17.26, CC13.3
/GFX/SYNC: HH16.22, HH16.23
/GFX/VA0: B13.9, B17.15, D13.8, D14.8, D16.8, D17.8
/GFX/VA1: B13.11, B17.16, D13.7, D14.7, D16.7, D17.7
/GFX/VA2: B13.13, B17.17, D13.6, D14.6, D16.6, D17.6
/GFX/VA3: B13.3, B17.18, D13.5, D14.5, D16.5, D17.5
/GFX/VA4: B13.5, B17.19, D13.4, D14.4, D16.4, D17.4
/GFX/VA5: B13.7, B17.20, D13.3, D14.3, D16.3, D17.3
/GFX/VA6: B17.21, CC13.5, D13.2, D14.2, D16.2, D17.2
/GFX/VA7: B17.22, CC13.7, D13.1, D14.1, D16.1, D17.1
/GFX/VA8: B17.23, CC13.9, D13.23, D14.23, D16.23, D17.23
/GFX/VA9: B17.24, CC13.11, D13.22, D14.22, D16.22, D17.22
/GFX/VA10: B17.25, CC13.13, D13.19, D14.19, D16.19, D17.19
/GFX/VD0: A16.14, B17.14, D16.9, D17.9, E10.17
/GFX/VD1: A16.17, B17.13, D16.10, D17.10, E10.18
/GFX/VD2: A16.3, B17.12, D16.11, D17.11, E10.11
/GFX/VD3: A16.4, B17.11, D16.13, D17.13, E10.12
/GFX/VD4: A16.7, B17.10, D16.14, D17.14, E10.13
/GFX/VD5: A16.8, B17.9, D16.15, D17.15, E10.14
/GFX/VD6: A16.13, B17.8, D16.16, D17.16, E10.15
/GFX/VD7: A16.18, B17.7, D16.17, D17.17, E10.16
/GFX/VD8: A15.4, B17.4, D13.9, D14.9, E11.17
/GFX/VD9: A15.3, D13.10, D14.10, E11.18
/GFX/VD10: A15.13, B15.10, D13.11, D14.11, E11.11
/GFX/VD11: A15.14, B15.9, D13.13, D14.13, E11.12
/GFX/VD12: A15.11, B15.8, D13.14, D14.14, E11.13
/GFX/VD13: A15.6, B15.7, D13.15, D14.15, E11.14
/GFX/VD14: B15.6, B17.59, D13.16, D14.16, E11.15
/GFX/VD15: B15.5, B17.60, D13.17, D14.17, E11.16
/GFX/~GCE: A4.20, A7.20, A10.20, A13.20, A15.10, B1.11
/GFX/~GOE: A2.22, A4.22, A5.22, A7.22, A8.22, A10.22, A12.22, A13.22
/GFX/~HBLK: B17.55, HH16.19
/GFX/~VBLK: B1.13, B17.58
/GFX/~VSYNC: B17.56, HH16.20
/IO/1P_BTN_1_B: H5.5, J6.14
/IO/1P_BTN_2_B: H5.11, J4.15
/IO/1P_BTN_3_B: H5.12, J4.14
/IO/1P_DOWN_B: H5.14, J4.13
/IO/1P_LEFT: G6.11, J4.7
/IO/1P_LEFT_B: H5.17, J4.10
/IO/1P_RIGHT: G6.1, J4.6
/IO/1P_RIGHT_B: H5.16, J4.11
/IO/1P_START_B: H5.2, J6.15
/IO/1P_UP_B: H5.15, J4.12
/IO/2P_BTN_1_B: H5.13, J6.10
/IO/2P_BTN_2_B: H5.3, J2.14
/IO/2P_BTN_3_B: H5.4, J2.15
/IO/2P_DOWN_B: H5.6, J2.13
/IO/2P_LEFT: G6.13, J2.7
/IO/2P_LEFT_B: H5.9, J2.10
/IO/2P_RIGHT: G6.3, J2.6
/IO/2P_RIGHT_B: H5.8, J2.11
/IO/2P_START_B: H5.10, J6.11
/IO/2P_UP_B: H5.7, J2.12
/IO/COINGND: G5.24, J11.10
/IO/COIN_1_B: G5.1, H9.8, J11.25
/IO/COIN_2_B: G5.39, H9.9, J11.26
/IO/P10: G5.27, H5.28, H5.44
/IO/P11: G5.28, H5.29, H5.45
/IO/P12: G5.29, H5.30, H5.46
/IO/P13: G5.30, H5.31, H5.47
/IO/P14: G5.31, H5.32, H5.48
/IO/P15: G5.32, H5.33, H5.49
/IO/P16: G5.33, H5.34, H5.50
/IO/P17: G5.34, H5.35, H5.51
/IO/P20: G5.21, H5.37
/IO/P21: G5.22, H5.41
/IO/P22: G5.23, H5.40
/IO/P24: D7.11, G5.35
/IO/P25: D7.8, G5.36
/IO/P26: D7.2, G5.37
/IO/P27: D7.5, G5.38
/IO/RESET: D7.3, D7.6, D7.9, D7.12, J9.6
/IO/SERVICE_B: H5.25, H9.7, J6.13
/IO/TILT_B: H5.24, J6.12
/IO/~1P_LEFT: G6.10, H5.21, H9.1
/IO/~1P_RIGHT: G6.2, H5.20, H9.2
/IO/~2P_LEFT: G6.12, H5.19, H9.4
/IO/~2P_RIGHT: G6.4, H5.18, H9.5
/Misc/MCK6M: B4.11, B12.17, F9.6
/Misc/SCK6M: B3.3, B3.11, B12.15, D5.6
GND: A2.14, A4.14, A5.14, A7.14, A8.14, A10.14, A12.14, A13.14, B8.15, B9.15, B10.15, B11.15, B12.19, B15.32, B15.64, B17.31, B17.32, B17.45, B17.64, C3.10, CC2.10, CC7.14, CC9.14, CC9.20, CC11.14, CC11.20, D5.29, D6.10, D13.12, D13.20, D14.12, D14.20, D16.12, D16.20, D17.12, D17.20, E3.14, E3.20, E9.10, F9.29, F13.5, F15.10, F15.15, F17.10, F17.15, G5.7, G5.20, G6.5, G6.9, G9.1, G14.7, H5.1, H5.26, H5.36, H5.38, H5.39, H5.42, H5.43, H9.12, H11.6, H15.8, H16.8, H17.8, HH16.21, J2.9, J2.16, J4.9, J4.16, J6.9, J6.16, J9.4, J11.1, J11.6, J11.11, J11.15, J11.22, J11.24, J16.4, J16.9
unnamed: B1.8, CC6.4
unnamed: B3.5, B3.12
unnamed: B1.12, B4.3, B7.11
unnamed: B4.6, F9.16
unnamed: B4.1, F9.20
unnamed: B2.6, B4.12
unnamed: B2.10, B5.10
unnamed: B6.3, CC6.12
unnamed: B6.6, CC6.1
unnamed: B7.8, D5.16
unnamed: B7.13, D5.20
unnamed: B15.4, B17.61
unnamed: B15.19, B17.46
unnamed: B15.18, B17.47
unnamed: B15.17, B17.48
unnamed: B15.16, B17.49
unnamed: B15.15, B17.50
unnamed: B15.14, B17.51
unnamed: B15.13, B17.52
unnamed: B15.12, B17.53
unnamed: B15.11, B17.54
unnamed: F13.1, F13.4
unnamed: CC6.6, D13.21, D14.21, D16.21, D17.21
unnamed: B2.13, E1.5
unnamed: CC6.11, E10.19
unnamed: CC6.3, E11.19
unnamed: F13.3, F13.12
unnamed: F13.10, G5.3
unnamed: G9.18, G9.19, G9.20
unnamed: G9.23, H11.4
unnamed: G9.39, H11.5
unnamed: G9.22, H11.3
unnamed: B1.6, G14.2
unnamed: F13.9, G14.5
unnamed: F13.2, G14.1
unnamed: H5.22, J11.13
unnamed: H5.23, J11.14
unnamed: H11.2, H12.3
unnamed: H11.8, H12.6, H12.7
unnamed: H11.7, H12.5
unnamed: H12.1, H12.2
unnamed: H17.3, HH16.25
unnamed: H17.4, HH16.26
unnamed: H17.5, HH16.27
unnamed: H17.6, HH16.28
unnamed: H17.7, HH16.29
unnamed: H17.2, HH16.24
unnamed: H16.3, HH16.31
unnamed: H16.4, HH16.32
unnamed: H16.5, HH16.33
unnamed: H16.6, HH16.34
unnamed: H16.7, HH16.35
unnamed: H16.2, HH16.30
unnamed: H15.3, HH16.37
unnamed: H15.4, HH16.38
unnamed: H15.5, HH16.39
unnamed: H15.6, HH16.40
unnamed: H15.7, HH16.41
unnamed: H15.2, HH16.36
unnamed: D7.13, J11.17
unnamed: D7.10, J11.8
unnamed: D7.1, J11.23
unnamed: D7.4, J11.20
VCC: A2.28, A4.28, A5.28, A7.28, A8.28, A10.28, A12.28, A13.28, A15.1, A16.1, B3.1, B3.10, B3.13, B4.2, B4.4, B4.10, B4.13, B7.10, B7.12, B12.1, B15.1, B15.33, B17.1, B17.33, C3.20, CC2.20, CC7.26, CC7.28, CC9.28, CC11.28, D5.11, D5.25, D6.20, D13.24, D14.24, D16.24, D17.24, E3.28, E9.20, F9.11, F9.25, F15.20, F17.20, G5.5, G5.26, G5.40, G9.21, G14.14, H5.27, H5.52, H9.24, H11.1, HH16.18, HH16.42, J2.1, J2.8, J4.1, J4.8, J6.1, J6.8, J9.8, J11.5, J11.9, J11.21, J16.10

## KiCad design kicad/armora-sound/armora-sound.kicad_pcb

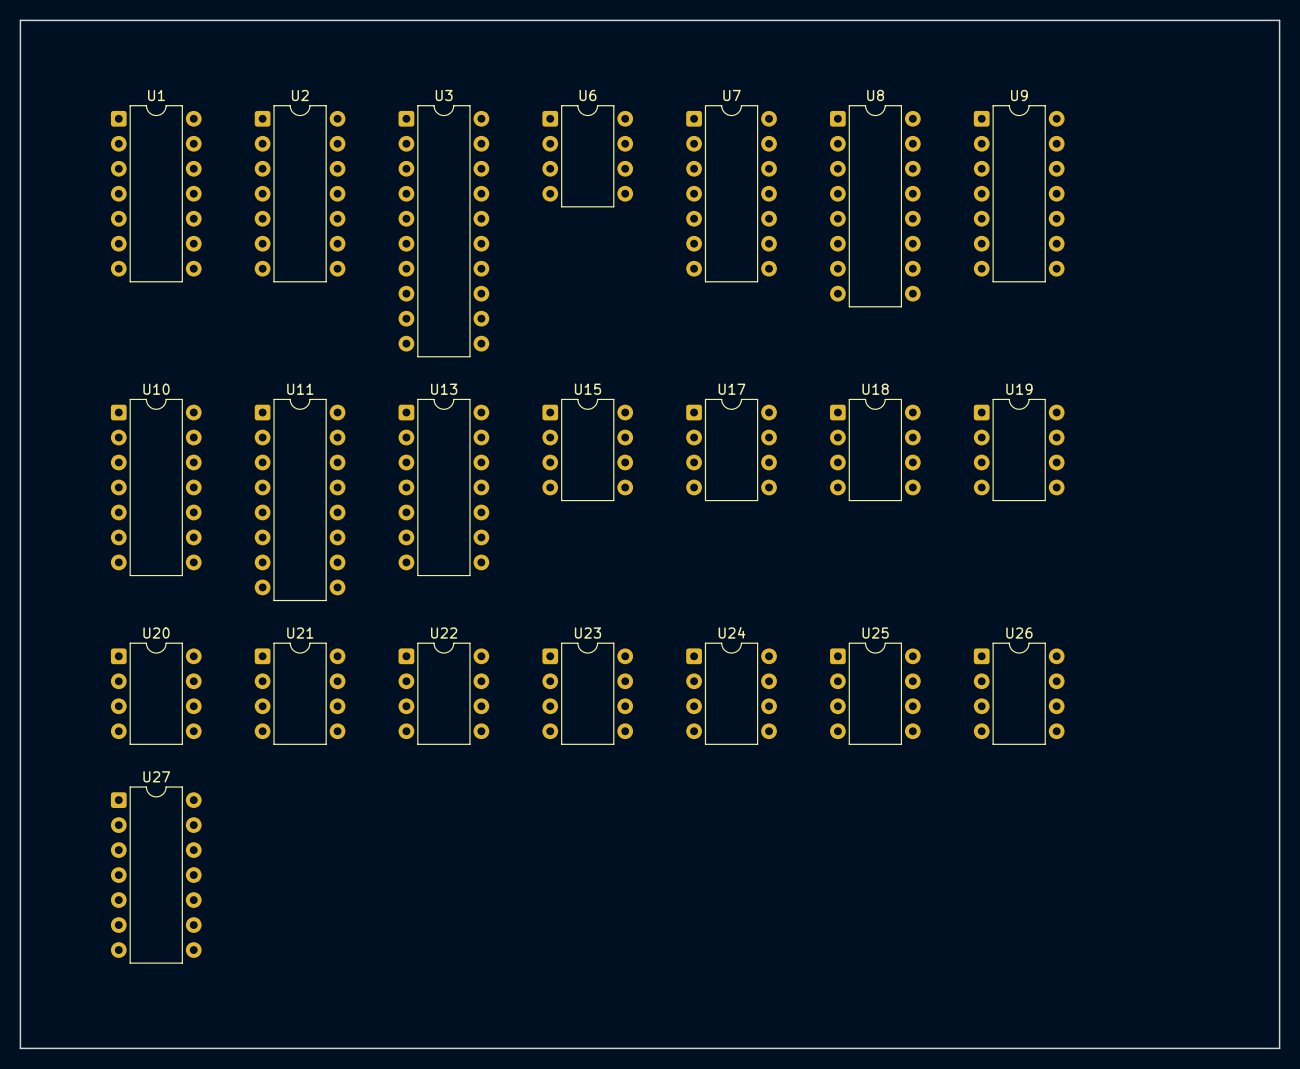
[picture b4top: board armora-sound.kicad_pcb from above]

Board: 2 copper layers, 128.0 x 104.5 mm, 22 parts (0 on the bottom side), 45 nets, no tracks yet.

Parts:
U1, U27: 7414; DIP-14_W7.62mm
U2: 74LS164; DIP-14_W7.62mm
U3: 74LS377; DIP-20_W7.62mm
U6, U23: LM555; DIP-8_W7.62mm
U7: 7406; DIP-14_W7.62mm
U8, U11: 74LS163; DIP-16_W7.62mm
U9: 74LS00; DIP-14_W7.62mm
U10, U13: 74LS393; DIP-14_W7.62mm
U15: LM566; DIP-8_W7.62mm
U17: S2688; DIP-8_W7.62mm
U18, U24, U25, U26: TL081; DIP-8_W7.62mm
U19, U20, U21, U22: CA3080; DIP-8_W7.62mm

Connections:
+5V: U1.14, U2.14, U3.20, U6.8, U7.14, U8.16, U9.14, U10.14, U11.16, U13.14, U23.8, U27.14
+15V: U15.8, U17.4, U18.7, U19.7, U20.7, U21.7, U22.7, U24.7, U25.7, U26.7
-15V: U18.4, U19.4, U20.4, U21.4, U22.4, U24.4, U25.4, U26.4
BEEP_EN: U23.4, U27.8
CHOPPER_SW: U7.3, U27.4
GND: U1.7, U2.7, U3.1, U3.10, U6.1, U7.7, U8.8, U9.7, U10.2, U10.7, U10.12, U11.5, U11.6, U11.8, U13.7, U15.1, U17.1, U17.2, U23.1, U26.3, U27.7
HI: U2.1, U2.9, U8.1, U8.7, U8.10, U11.1, U11.3, U11.4, U11.7, U11.10
NOISE: U18.2, U18.6
unnamed: U6.2, U6.6
unnamed: U23.2, U23.6
unnamed: U25.2, U25.6
unnamed: U7.8, U13.12
unnamed: U19.6, U20.6, U21.6, U22.6, U25.3
unnamed: U7.12, U13.2
unnamed: U1.1, U1.12
unnamed: U1.2, U2.2
unnamed: U1.3, U11.15
unnamed: U1.4, U11.9
unnamed: U1.6, U2.8
unnamed: U1.8, U8.2
unnamed: U1.9, U6.3
unnamed: U1.5, U1.10
unnamed: U2.3, U3.3
unnamed: U2.4, U3.4
unnamed: U2.5, U3.7
unnamed: U2.6, U3.8
unnamed: U2.10, U3.13
unnamed: U2.11, U3.14
unnamed: U2.12, U3.17
unnamed: U2.13, U3.18
unnamed: U3.12, U8.6
unnamed: U3.15, U8.5
unnamed: U3.16, U8.4
unnamed: U3.19, U8.3
unnamed: U8.9, U9.3
unnamed: U8.15, U9.1, U9.2, U10.1, U11.2
unnamed: U9.9, U10.6, U13.13
unnamed: U9.8, U10.13
unnamed: U9.10, U11.11
unnamed: U3.11, U27.6
unnamed: U27.5, U27.10
SH2_1: U7.5, U13.8
SH2_3: U7.11, U7.13, U13.9
SH2_5: U7.6, U7.10
TANK_EN: U6.4, U7.9, U27.12
